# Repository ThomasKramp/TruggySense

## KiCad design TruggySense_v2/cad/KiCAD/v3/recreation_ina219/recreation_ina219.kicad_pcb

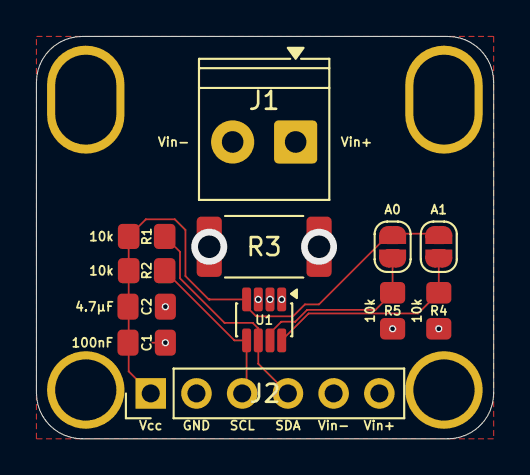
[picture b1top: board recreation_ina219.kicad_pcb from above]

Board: 6 copper layers, 25.4 x 22.4 mm, 12 parts (0 on the bottom side), 8 nets.

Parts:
C1: 100nF; C_0805_2012Metric_Pad1.18x1.45mm_HandSolder
C2: 4.7µF; C_0805_2012Metric_Pad1.18x1.45mm_HandSolder
J1: IN; TerminalBlock_Phoenix_PT-1,5-2-3.5-H_1x02_P3.50mm_Horizontal
J2: INA_IO; PinHeader_1x06_P2.54mm_Vertical
JP1: A1; SolderJumper-2_P1.3mm_Open_RoundedPad1.0x1.5mm
JP2: A0; SolderJumper-2_P1.3mm_Open_RoundedPad1.0x1.5mm
R1, R2, R4, R5: 10k; R_0805_2012Metric_Pad1.20x1.40mm_HandSolder
R3: 100m; R_2512_6332Metric_Pad1.40x3.35mm_HandSolder
U1: INA219AxDCN; SOT-23-8

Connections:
/GND: C1.2, C2.2, J2.2, R4.2, R5.2, U1.3 (GND)
/IN+: J1.1, J2.6, R3.1, U1.1 (IN+)
/IN-: J1.2, J2.5, R3.2, U1.2 (IN-)
/SCL: J2.3, R2.2, U1.5 (SCL)
/SDA: J2.4, R1.2, U1.6 (SDA)
/VCC: C1.1, C2.1, J2.1, JP1.2 (B), JP2.2 (B), R1.1, R2.1, U1.4 (VS)
unnamed: JP1.1 (A), R4.1, U1.8 (A1)
unnamed: JP2.1 (A), R5.1, U1.7 (A0)
